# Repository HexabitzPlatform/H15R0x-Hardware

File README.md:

# H15R0x-Hardware
Hexabitz Bipolar +/-10V Analog Output Module Hardware Design

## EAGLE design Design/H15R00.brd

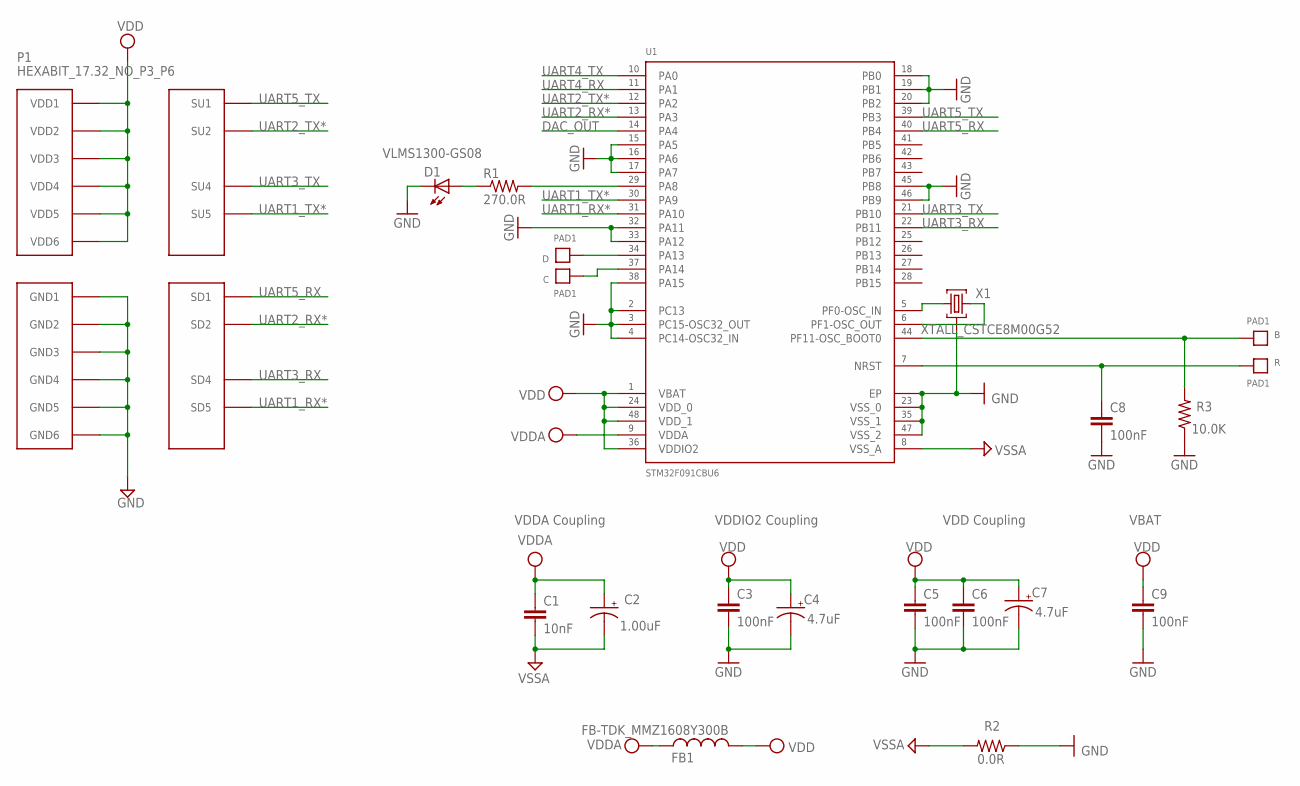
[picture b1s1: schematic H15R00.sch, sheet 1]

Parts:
B: PAD1
C: PAD1
C1: 10nF; C-0603; TOLERANCE 10%; VOLTAGE_RATING 50V; MPN C0603C103K5RACTU
C2: 1.00uF; C-0805-POL; TOLERANCE 10%; VOLTAGE_RATING 16V; MPN CC0805KKX7R7BB105
C3, C6, C8: 100nF; C-0603; TOLERANCE 10%; VOLTAGE_RATING 10V; MPN C0603C104K8RACTU
C4, C7: 4.7uF; C-0805-POL; TOLERANCE 10%; VOLTAGE_RATING 25V; MPN GRM21BC81E475KA12L
C5: 100nF; C-0603; TOLERANCE 10%; VOLTAGE_RATING 10; MPN C0603C104K8RACTU
C9: 100nF; C-0603; TOLERANCE 10V; VOLTAGE_RATING 10%; MPN C0603C104K8RACTU
D: PAD1
D1: VLMS1300-GS08; MPN VLMS1300-GS08
FB1: FB-TDK_MMZ1608Y300B; MPN MMZ1608Y300B
P1: HEXABIT_17.32_NO_P3_P6
R: PAD1
R1: 270.0R; R-0603; TOLERANCE 1%; MPN RC0603FR-07270RL
R2: 0.0R; R-0603; MPN RC0603JR-070RL
R3: 10.0K; R-0603; TOLERANCE 5%; MPN RC0603JR-0710KL
U1: STM32F091CBU6
X1: XTALL_CSTCE8M00G52

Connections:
B1: B.P$1, B.P$2, R3.2, U1.P$44 (PF11-OSC_BOOT0)
DAC_OUT: U1.P$14 (PA4); also elsewhere on the board
GND: C3.2, C4.2 (-), C5.2, C6.2, C7.2 (-), C8.2, C9.2, D1.C, P1.PAD_PD7 (GND1), P1.PAD_PD8 (GND2), P1.PAD_PD9 (GND3), P1.PAD_PD10 (GND4), P1.PAD_PD11 (GND5), P1.PAD_PD12 (GND6), R2.1, R3.1, U1.EP, U1.P$2 (PC13), U1.P$3 (PC14-OSC32_IN), U1.P$4 (PC15-OSC32_OUT), U1.P$15 (PA5), U1.P$16 (PA6), U1.P$17 (PA7), U1.P$18 (PB0), U1.P$19 (PB1), U1.P$20 (PB2), U1.P$23 (VSS_0), U1.P$32 (PA11), U1.P$33 (PA12), U1.P$35 (VSS_1), U1.P$38 (PA15), U1.P$45 (PB8), U1.P$46 (PB9), U1.P$47 (VSS_2), X1.P$2 (2)
unnamed: R1.2, U1.P$29 (PA8)
unnamed: D1.A, R1.1
unnamed: U1.P$5 (PF0-OSC_IN), X1.P$1 (1)
unnamed: U1.P$6 (PF1-OSC_OUT), X1.P$3 (3)
unnamed: D.P$1, D.P$2, U1.P$34 (PA13)
unnamed: C.P$1, C.P$2, U1.P$37 (PA14)
R1: C8.1, R.P$1, R.P$2, U1.P$7 (NRST)
UART1_RX*: P1.PAD_PD5 (SD5), U1.P$31 (PA10)
UART1_TX*: P1.PAD_PU5 (SU5), U1.P$30 (PA9)
UART2_RX*: P1.PAD_PD2 (SD2), U1.P$13 (PA3)
UART2_TX*: P1.PAD_PU2 (SU2), U1.P$12 (PA2)
UART3_RX: P1.PAD_PD4 (SD4), U1.P$22 (PB11)
UART3_TX: P1.PAD_PU4 (SU4), U1.P$21 (PB10)
UART4_RX: U1.P$11 (PA1)
UART4_TX: U1.P$10 (PA0)
UART5_RX: P1.PAD_PD1 (SD1), U1.P$40 (PB4)
UART5_TX: P1.PAD_PU1 (SU1), U1.P$39 (PB3)
VDD: C3.1, C4.1 (+), C5.1, C6.1, C7.1 (+), C9.1, FB1.2, P1.PAD_PU7 (VDD1), P1.PAD_PU8 (VDD2), P1.PAD_PU9 (VDD3), P1.PAD_PU10 (VDD4), P1.PAD_PU11 (VDD5), P1.PAD_PU12 (VDD6), U1.P$1 (VBAT), U1.P$24 (VDD_0), U1.P$36 (VDDIO2), U1.P$48 (VDD_1)
VDDA: C1.1, C2.1 (+), FB1.1, U1.P$9 (VDDA); also elsewhere on the board
VSSA: C1.2, C2.2 (-), R2.2, U1.P$8 (VSS_A); also elsewhere on the board

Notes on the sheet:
VDDA Coupling
VDDIO2 Coupling
VDD Coupling
VBAT

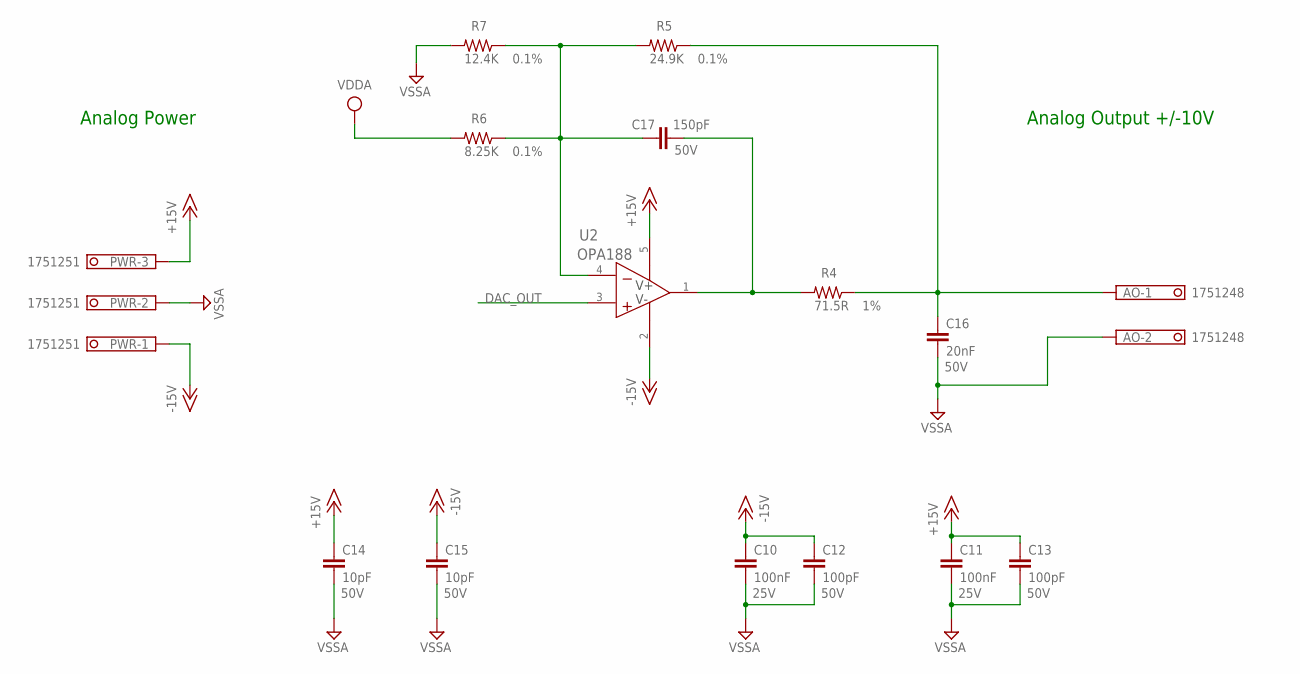
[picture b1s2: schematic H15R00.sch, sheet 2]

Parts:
AO: 1751248; CON-PHOENIX-350_1751248; MPN 1751248
C10, C11: 100nF; C-0603; TOLERANCE 10%; VOLTAGE_RATING 25V; MPN GRM188R71E104KA01D
C12, C13: 100pF; C-0603; TOLERANCE 5%; VOLTAGE_RATING 50V; MPN 06035A101JAT2A
C14, C15: 10pF; C-0603; TOLERANCE 5%; VOLTAGE_RATING 50V; MPN GRM1885C1H100JA01D
C16: 20nF; C-0603; TOLERANCE 10%; VOLTAGE_RATING 50V; MPN CL10B203KB8NNNC
C17: 150pF; C-0603; TOLERANCE 1%; VOLTAGE_RATING 50V; MPN C1608C0G1H151F080AA
PWR: 1751251; MPN 1751251
R4: 71.5R; R-0603; TOLERANCE 1%; MPN ERJ-3EKF71R5V
R5: 24.9K; R-0603; TOLERANCE 0.1%; MPN ERA-3AEB2492V
R6: 8.25K; R-0603; TOLERANCE 0.1%; MPN ERA-3AEB8251V
R7: 12.4K; R-0603; TOLERANCE 0.1%; MPN ERA-3AEB1242V
U2: OPA188; DBV0005A_N

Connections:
+15V: C11.1, C13.1, C14.1, PWR.3, U2.5 (V+)
-15V: C10.1, C12.1, C15.1, PWR.1, U2.2 (V-)
DAC_OUT: U2.3 (IN+); also elsewhere on the board
unnamed: AO.1, C16.1, R4.1, R5.1
unnamed: C17.2, R4.2, U2.1 (OUT)
unnamed: C17.1, R5.2, R6.1, R7.1, U2.4 (IN-)
VDDA: R6.2; also elsewhere on the board
VSSA: AO.2, C10.2, C11.2, C12.2, C13.2, C14.2, C15.2, C16.2, PWR.2, R7.2; also elsewhere on the board

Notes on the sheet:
Analog Output +/-10V
Analog Power

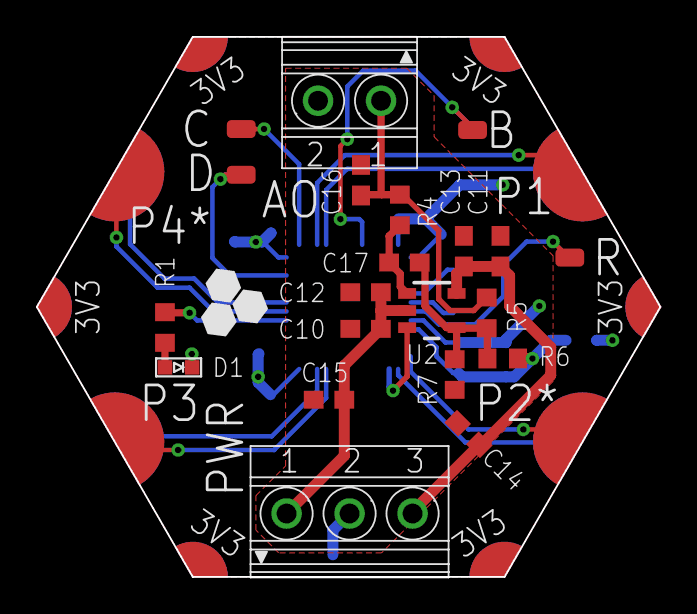
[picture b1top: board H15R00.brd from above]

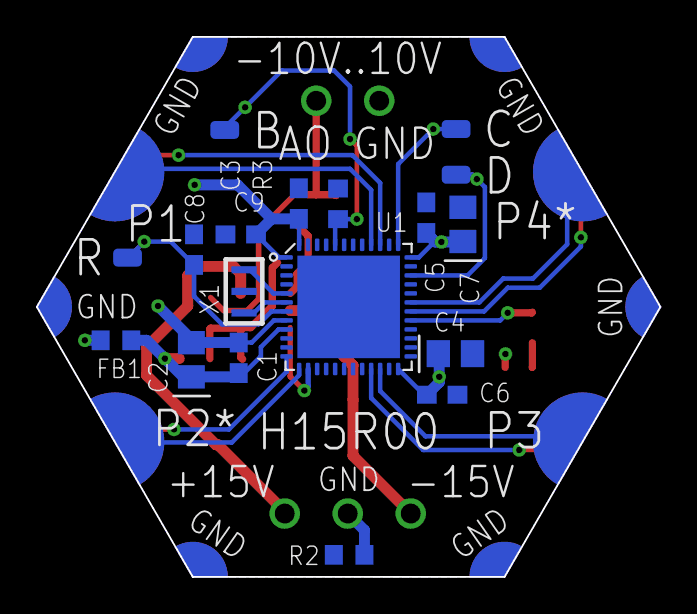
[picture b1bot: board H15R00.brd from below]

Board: 2 copper layers, 34.6 x 30.0 mm, 36 parts (14 on the bottom side), 26 nets.

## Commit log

2019-12-13 Generated seed files from the script
2019-12-13 Finished schematics
2019-12-16 Placed all components Routed analog part and most digital Added VSSA polygon
2019-12-16 Finished routing and silkscreen
2019-12-16 Solved DRC Generated gerber, drill, pick n place and schematics Generated BOM First release Ver 0
2020-05-09 Fix BOM
